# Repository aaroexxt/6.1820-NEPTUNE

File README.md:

# 6.1820-NEPTUNE
6.1820 final project - Aaron Becker and Nora Bulovic

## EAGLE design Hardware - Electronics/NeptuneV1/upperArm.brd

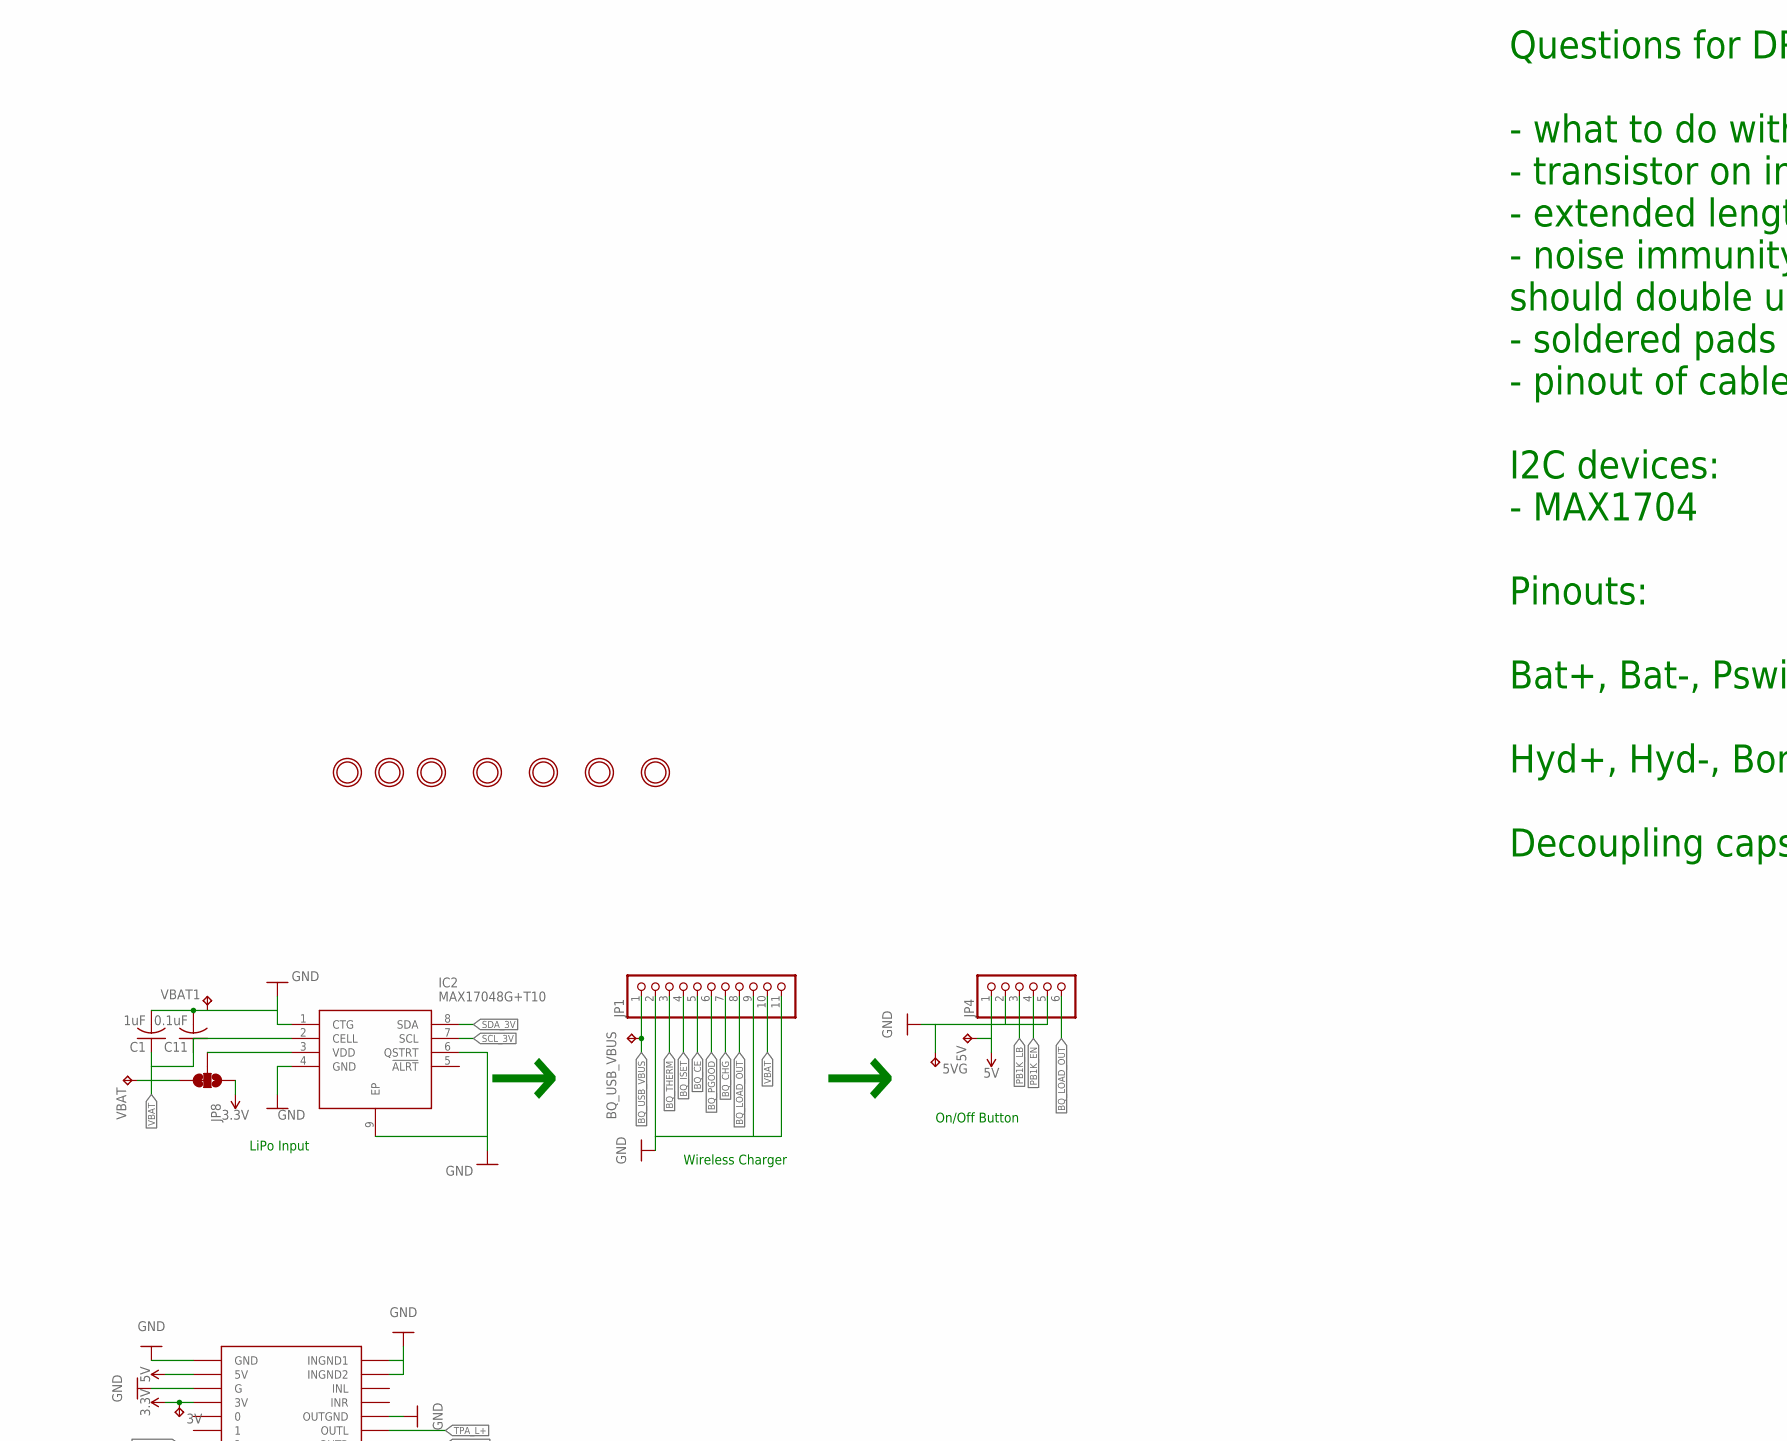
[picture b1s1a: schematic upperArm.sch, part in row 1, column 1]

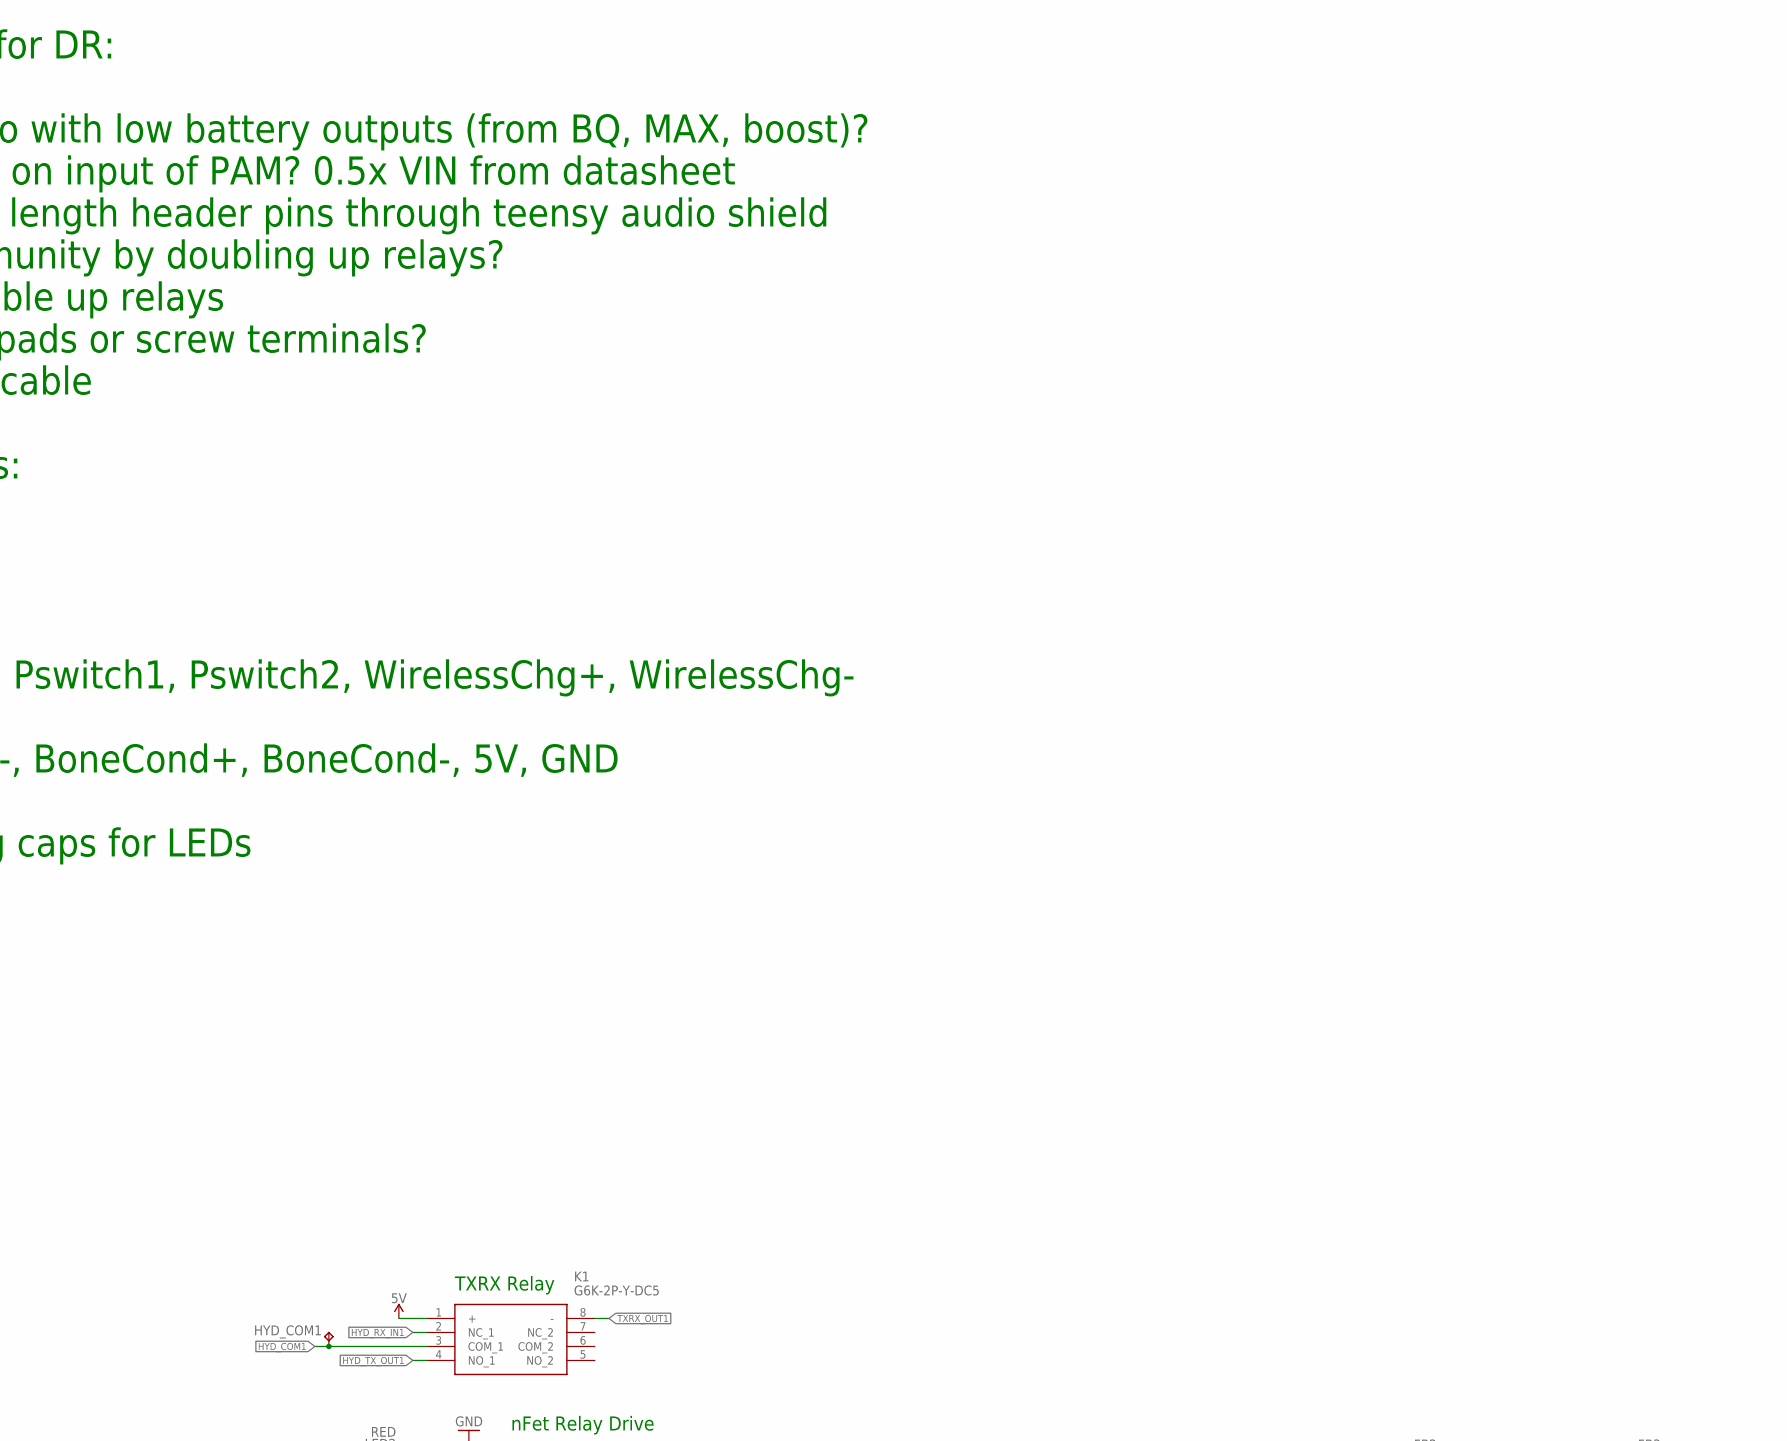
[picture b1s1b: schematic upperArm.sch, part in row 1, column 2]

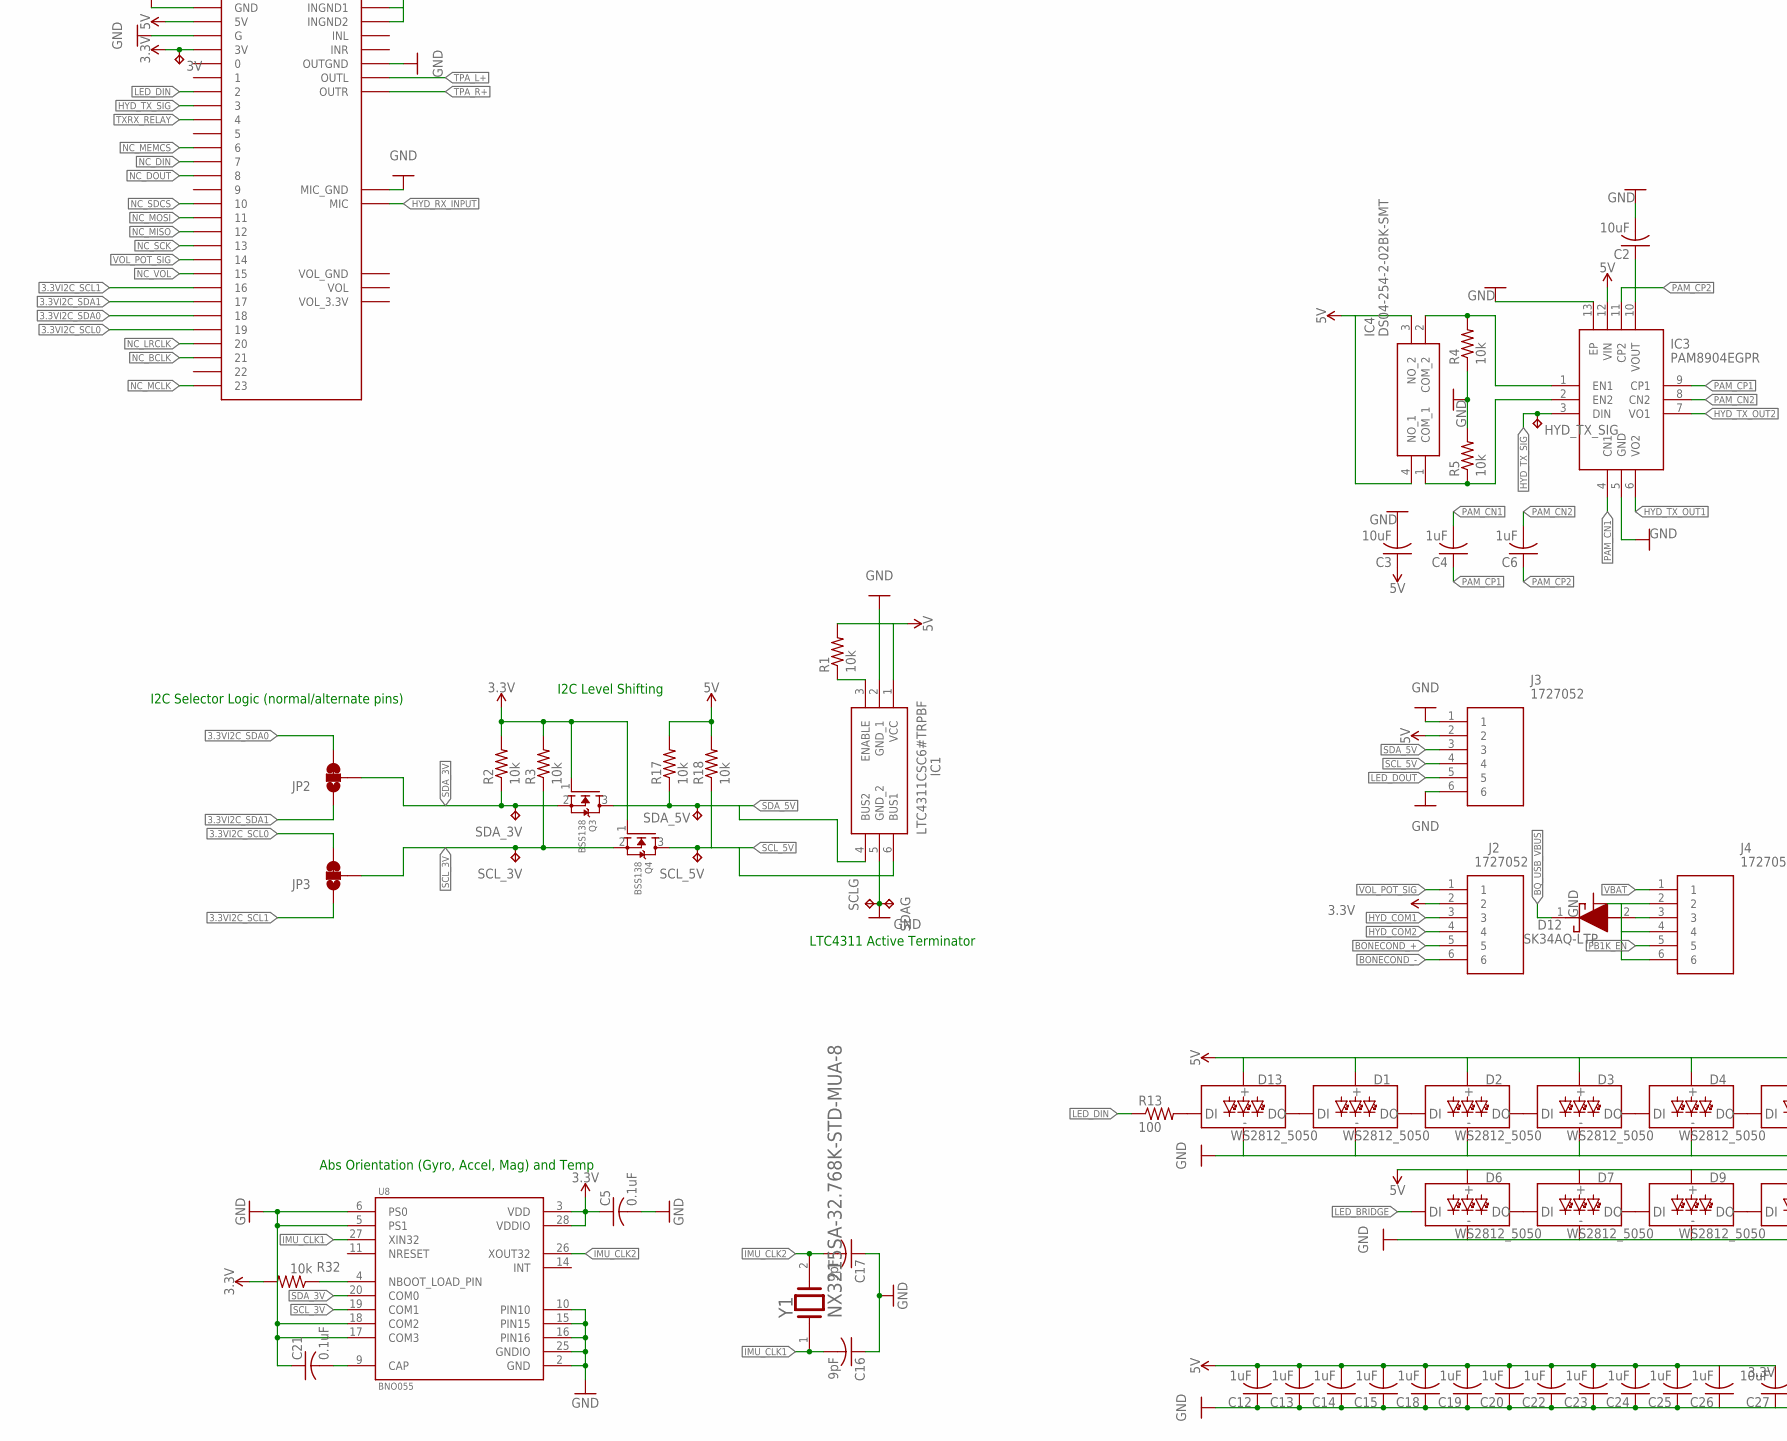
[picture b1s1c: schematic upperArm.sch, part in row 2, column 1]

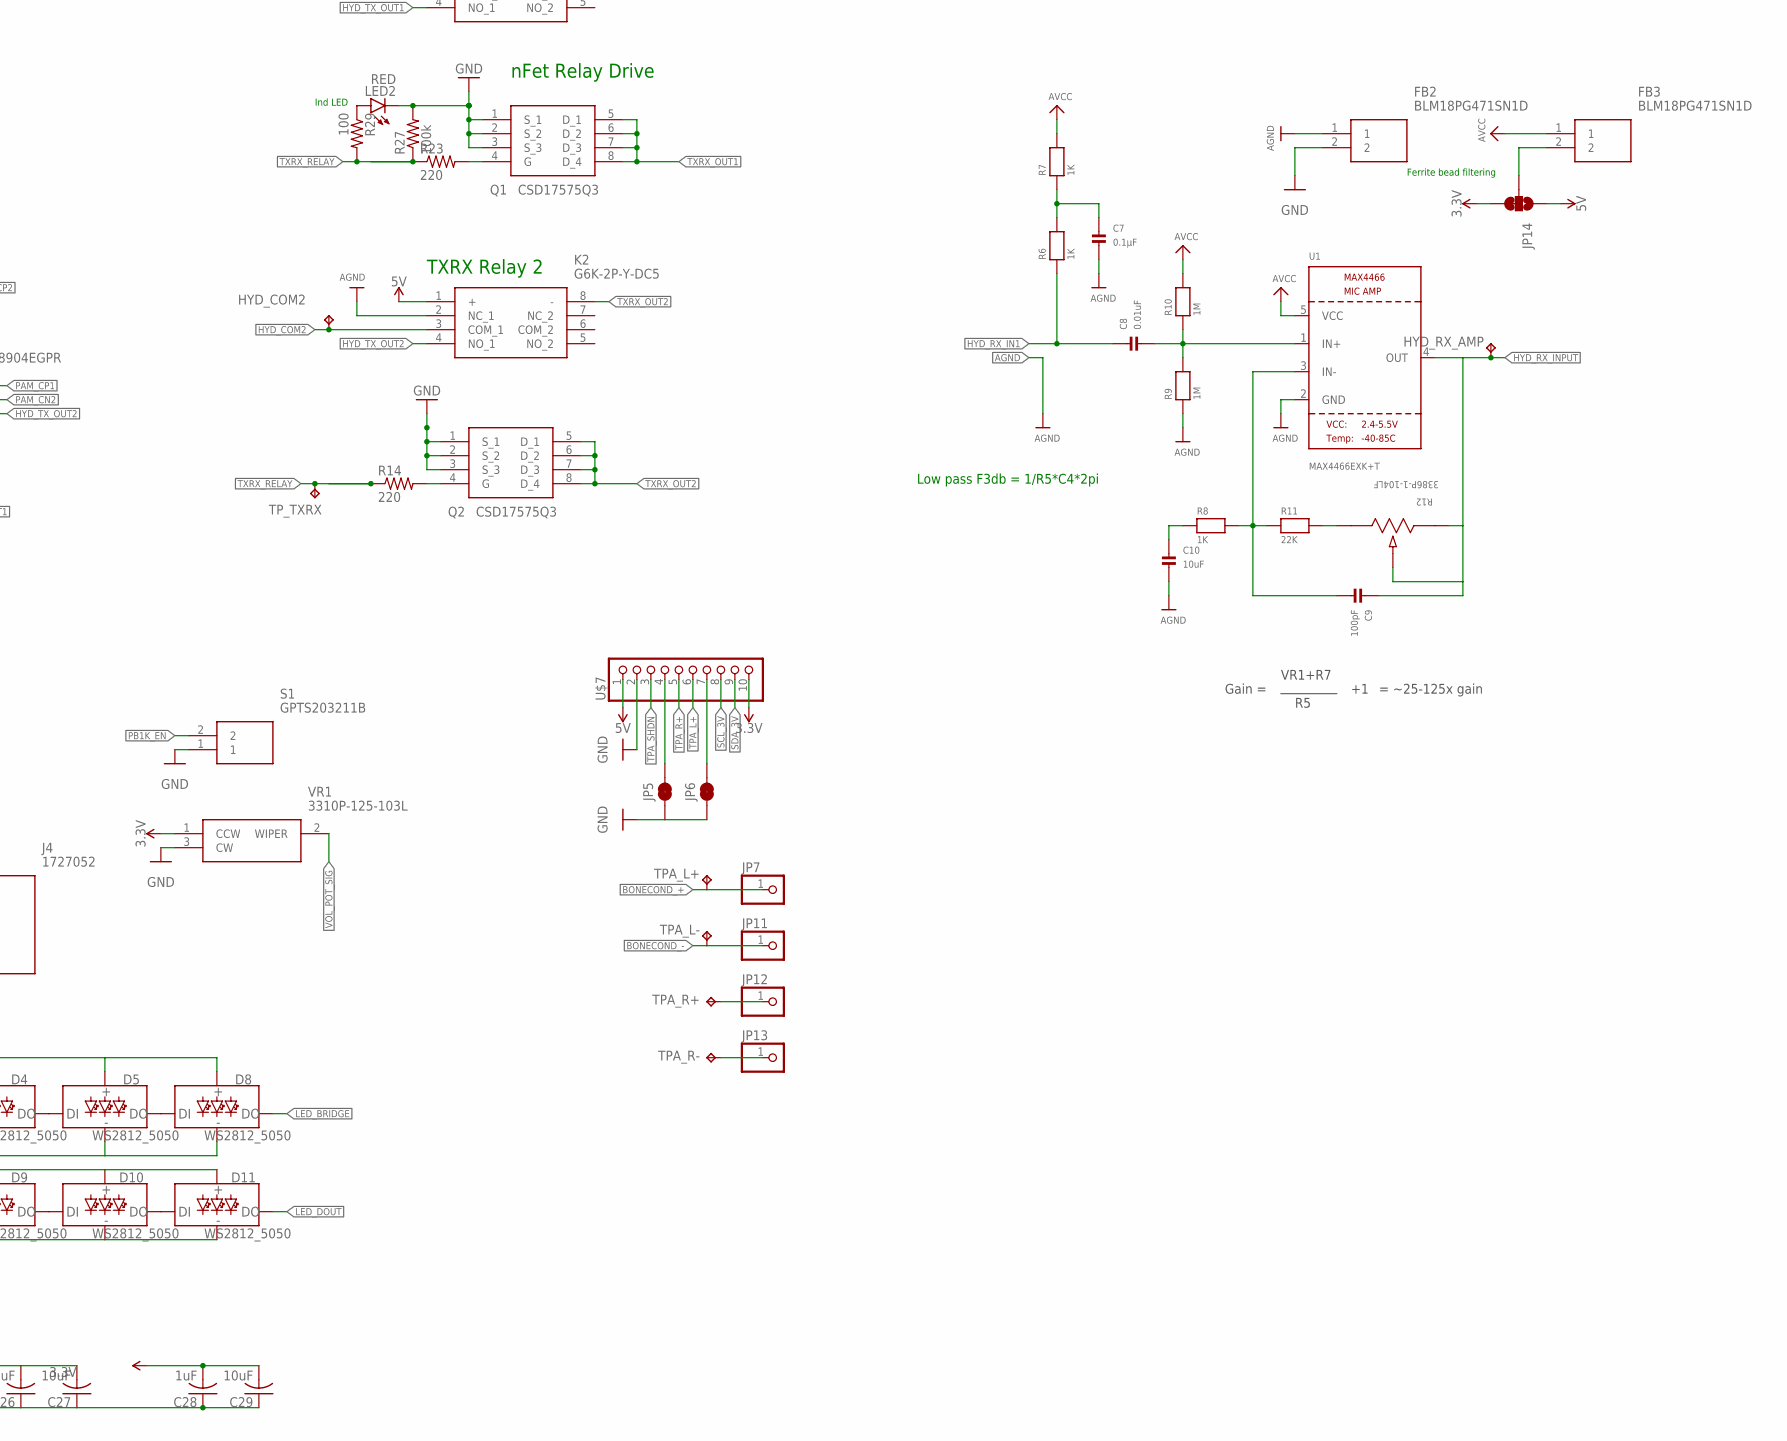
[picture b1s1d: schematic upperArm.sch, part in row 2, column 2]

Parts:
3V, 5V, 5VG: TPB1,27; B1,27
BQ_USB_VBUS: TPB1,27; B1,27
C1, C4, C6, C12, C13, C14, C15, C18, C19, C20, C22, C23, C24, C25, C26, C28: 1uF; C0805
C2, C3, C27, C29: 10uF; C0805
C5, C11, C21: 0.1uF; C0805
C7: 0.1µF; 0805
C8: 0.01uF; 0805
C9: 100pF; 0805
C10: 10uF; 0805
C16, C17: 9pF; C0805
D1, D2, D3, D4, D5, D6, D7, D8, D9, D10, D11, D13: WS2812_5050; WS2812-5X5-4PIN
D12: SK34AQ-LTP; DIOM5226X244N
FB2, FB3: BLM18PG471SN1D; BLM18SP221SN1B
HYD_COM1, HYD_COM2: TPB1,27; B1,27
HYD_RX_AMP: TPB1,27; B1,27
HYD_TX_SIG: TPB1,27; B1,27
IC1: LTC4311CSC6#TRPBF; SOT65P210X100-6N
IC2: MAX17048G+T10; SON50P200X200X80-9N
IC3: PAM8904EGPR; QFN40P200X200X80-13N
IC4: DS04-254-2-02BK-SMT; DS04254202BKSMT
J2, J3, J4: 1727052
JP1: PINHD-1X11; 1X11
JP2, JP3, JP8, JP14: JUMPER-SMT_3_1-NC_TRACE_NO-SILK; SMT-JUMPER_3_1-NC_TRACE_NO-SILK
JP4: PINHD-1X6; 1X06
JP5, JP6: JUMPER-SMT_2_NC_TRACE_NO-SILK; SMT-JUMPER_2_NC_TRACE_NO-SILK
JP7, JP11, JP12, JP13: PINHD-1X1; 1X01
K1, K2: G6K-2P-Y-DC5; G6K2PYDC12
LED2: RED; CHIP-LED0805
Q1, Q2: CSD17575Q3; CSD16327
Q3, Q4: BSS138; SOT23-WIDE
R1, R2, R3, R4, R5, R17, R18, R32: 10k; R0805
R6, R7, R8: 1K; 0805
R9, R10: 1M; 0805
R11: 22K; 0805
R12: 3386P-1-104LF; POT_3386P
R13: 100; R0603
R14, R23: 220; R0805
R27: 100k; R0805
R29: 100; R0805
S1: GPTS203211B
SCLG: TPB1,27; B1,27
SCL_3V, SCL_5V: TPB1,27; B1,27
SDAG: TPB1,27; B1,27
SDA_3V, SDA_5V: TPB1,27; B1,27
TPA_L+: TPB1,27; B1,27
TPA_L-: TPB1,27; B1,27
TPA_R+: TPB1,27; B1,27
TPA_R-: TPB1,27; B1,27
TP_TXRX: TPB1,27; B1,27
U1: MAX4466EXK+T; SC70-5
U8: BNO055; LGA28R50P4X10_380X520X100
U$1: AUDIOSHIELD
U$7: PINHD-1X10; 1X10
U$11, U$14, U$15, U$16, U$17, U$18, U$19: MOUNTINGHOLE2.5; MOUNTINGHOLE_2.5_PLATED
VBAT, VBAT1: TPB1,27; B1,27
VR1: 3310P-125-103L; 3310P125103L
Y1: NDK_NX3215SA-32.768K-STD-MUA-9; NDK_NX3215SA-32.768K-STD-MUA-8_0

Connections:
3.3V: 3V.TP, C5.1, C28.2, C29.2, J2.2, JP8.1, JP14.3, Q3.1 (G), Q4.1 (G), R2.2, R3.2, R32.2, U8.3 (VDD), U8.28 (VDDIO), U$1.3V, U$7.10, VR1.1 (CCW)
3.3VI2C_SCL0: JP3.3, U$1.19
3.3VI2C_SCL1: JP3.1, U$1.16
3.3VI2C_SDA0: JP2.3, U$1.18
3.3VI2C_SDA1: JP2.1, U$1.17
5V: 5V.TP, C3.1, C12.2, C13.2, C14.2, C15.2, C18.2, C19.2, C20.2, C22.2, C23.2, C24.2, C25.2, C26.2, C27.2, D1.VCC, D2.VCC, D3.VCC, D4.VCC, D5.VCC, D6.VCC, D7.VCC, D8.VCC, D9.VCC, D10.VCC, D11.VCC, D13.VCC, IC1.1 (VCC), IC3.12 (VIN), IC4.3 (NO_2), IC4.4 (NO_1), J3.2, JP4.1, JP14.1, K1.1 (+), K2.1 (+), R1.2, R17.2, R18.2, U$1.5V, U$7.1
AGND: C7.2, C10.2, FB2.1, K2.2 (NC_1), R9.1, U1.2 (GND)
AVCC: FB3.1, R7.2, R10.2, U1.5 (VCC)
BONECOND_+: J2.5, JP7.1, TPA_L+.TP
BONECOND_-: J2.6, JP11.1, TPA_L-.TP
BQ_CE: JP1.5
BQ_CHG: JP1.7
BQ_ISET: JP1.4
BQ_LOAD_OUT: JP1.8, JP4.6
BQ_PGOOD: JP1.6
BQ_THERM: JP1.3
BQ_USB_VBUS: BQ_USB_VBUS.TP, D12.1 (K), JP1.1
GND: 5VG.TP, C1.2, C2.2, C3.2, C5.2, C11.2, C12.1, C13.1, C14.1, C15.1, C16.1, C17.1, C18.1, C19.1, C20.1, C21.1, C22.1, C23.1, C24.1, C25.1, C26.1, C27.1, C28.1, C29.1, D1.GND, D2.GND, D3.GND, D4.GND, D5.GND, D6.GND, D7.GND, D8.GND, D9.GND, D10.GND, D11.GND, D13.GND, FB2.2, IC1.2 (GND_1), IC1.5 (GND_2), IC2.1 (CTG), IC2.4 (GND), IC2.6 (QSTRT), IC2.9 (EP), IC3.5 (GND), IC3.13 (EP), J3.1, J3.6, J4.2, J4.4, J4.6, JP1.2, JP1.9, JP1.11, JP4.2, JP4.5, JP5.1, JP6.1, LED2.C, Q1.1 (S_1), Q1.2 (S_2), Q1.3 (S_3), Q2.1 (S_1), Q2.2 (S_2), Q2.3 (S_3), R4.1, R5.2, R27.2, S1.1, SCLG.TP, SDAG.TP, U8.2 (GND), U8.5 (PS1), U8.6 (PS0), U8.10 (PIN10), U8.15 (PIN15), U8.16 (PIN16), U8.17 (COM3), U8.18 (COM2), U8.25 (GNDIO), U$1.G, U$1.GND, U$1.GND_MIC (MIC_GND), U$1.INGND1, U$1.INGND2, U$1.OUTGND, U$7.2, VBAT1.TP, VR1.3 (CW)
HYD_COM1: HYD_COM1.TP, J2.3, K1.3 (COM_1)
HYD_COM2: HYD_COM2.TP, J2.4, K2.3 (COM_1)
HYD_RX_IN1: C8.1, K1.2 (NC_1), R6.1
HYD_RX_INPUT: C9.1, HYD_RX_AMP.TP, R12.1, R12.2, U1.4 (OUT), U$1.MIC
HYD_TX_OUT1: IC3.6 (VO2), K1.4 (NO_1)
HYD_TX_OUT2: IC3.7 (VO1), K2.4 (NO_1)
HYD_TX_SIG: HYD_TX_SIG.TP, IC3.3 (DIN), U$1.3
IMU_CLK1: C16.2, U8.27 (XIN32), Y1.1
IMU_CLK2: C17.2, U8.26 (XOUT32), Y1.2
LED_BRIDGE: D6.DI, D8.DO
LED_DIN: R13.1, U$1.2
LED_DOUT: D11.DO, J3.5
unnamed: IC1.3 (ENABLE), R1.1
unnamed: JP12.1, TPA_R+.TP
unnamed: JP13.1, TPA_R-.TP
unnamed: D6.DO, D7.DI
unnamed: IC2.3 (VDD), JP8.2
unnamed: Q2.4 (G), R14.2
unnamed: C2.1, IC3.10 (VOUT)
unnamed: D13.DI, R13.2
unnamed: JP5.2, U$7.4
unnamed: D1.DO, D2.DI
unnamed: IC3.1 (EN1), IC4.2 (COM_2), R4.2
unnamed: IC3.2 (EN2), IC4.1 (COM_1), R5.1
unnamed: FB3.2, JP14.2
unnamed: C7.1, R6.2, R7.1
unnamed: C8.2, R9.2, R10.1, U1.1 (IN+)
unnamed: D1.DI, D13.DO
unnamed: C9.2, R8.2, R11.1, U1.3 (IN-)
unnamed: C10.1, R8.1
unnamed: R11.2, R12.3
unnamed: D12.2 (A), J4.3
unnamed: D2.DO, D3.DI
unnamed: D3.DO, D4.DI
unnamed: D4.DO, D5.DI
unnamed: D5.DO, D8.DI
unnamed: D7.DO, D9.DI
unnamed: D9.DO, D10.DI
unnamed: D10.DO, D11.DI
unnamed: JP6.2, U$7.7
unnamed: C21.2, U8.9 (CAP)
unnamed: R32.1, U8.4 (NBOOT_LOAD_PIN)
unnamed: Q1.4 (G), R23.2
unnamed: LED2.A, R29.1
NC_BCLK: U$1.21
NC_DIN: U$1.7
NC_DOUT: U$1.8
NC_LRCLK: U$1.20
NC_MCLK: U$1.23
NC_MEMCS: U$1.6
NC_MISO: U$1.12
NC_MOSI: U$1.11
NC_SCK: U$1.13
NC_SDCS: U$1.10
NC_VOL: U$1.15
PAM_CN1: C4.2, IC3.4 (CN1)
PAM_CN2: C6.2, IC3.8 (CN2)
PAM_CP1: C4.1, IC3.9 (CP1)
PAM_CP2: C6.1, IC3.11 (CP2)
PB1K_EN: J4.5, JP4.4, S1.2
PB1K_LB: JP4.3
SCL_3V: IC2.7 (SCL), JP3.2, Q4.2 (S), R3.1, SCL_3V.TP, U8.19 (COM1), U$7.8
SCL_5V: IC1.6 (BUS1), J3.4, Q4.3 (D), R18.1, SCL_5V.TP
SDA_3V: IC2.8 (SDA), JP2.2, Q3.2 (S), R2.1, SDA_3V.TP, U8.20 (COM0), U$7.9
SDA_5V: IC1.4 (BUS2), J3.3, Q3.3 (D), R17.1, SDA_5V.TP
TPA_L+: U$1.OUTL, U$7.6
TPA_R+: U$1.OUTR, U$7.5
TPA_SHDN: U$7.3
TXRX_OUT1: K1.8 (-), Q1.5 (D_1), Q1.6 (D_2), Q1.7 (D_3), Q1.8 (D_4)
TXRX_OUT2: K2.8 (-), Q2.5 (D_1), Q2.6 (D_2), Q2.7 (D_3), Q2.8 (D_4)
TXRX_RELAY: R14.1, R23.1, R27.1, R29.2, TP_TXRX.TP, U$1.4
VBAT: C1.1, C11.1, IC2.2 (CELL), J4.1, JP1.10, JP8.3, VBAT.TP
VOL_POT_SIG: J2.1, U$1.14, VR1.2 (WIPER)

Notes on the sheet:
I2C Level Shifting
Abs Orientation (Gyro, Accel, Mag) and Temp
I2C Selector Logic (normal/alternate pins)
LTC4311 Active Terminator
Wireless Charger
On/Off Button
Questions for DR: - what to do with low battery outputs (from BQ, MAX, boost)? - transistor on input of PAM? 0.5x VIN from datasheet - extended length header pins through teensy audio shield - noise immunity by doubling up relays? should double up relays - soldered pads or screw terminals? - pinout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
LiPo Input
Gain =
VR1+R7
= ~25-125x gain
Low pass F3db = 1/R5*C4*2pi
nFet Relay Drive
Ind LED
TXRX Relay
Ferrite bead filtering
TXRX Relay 2

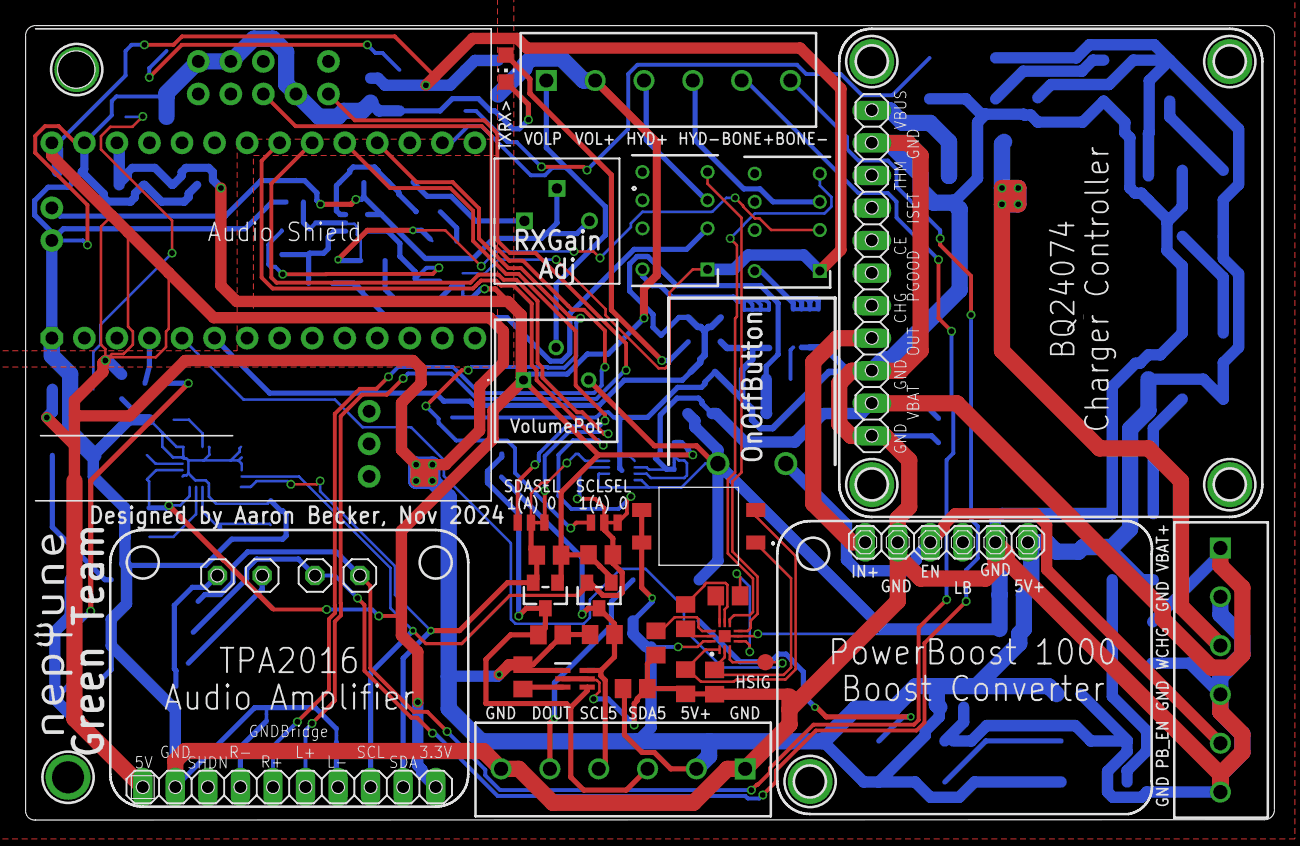
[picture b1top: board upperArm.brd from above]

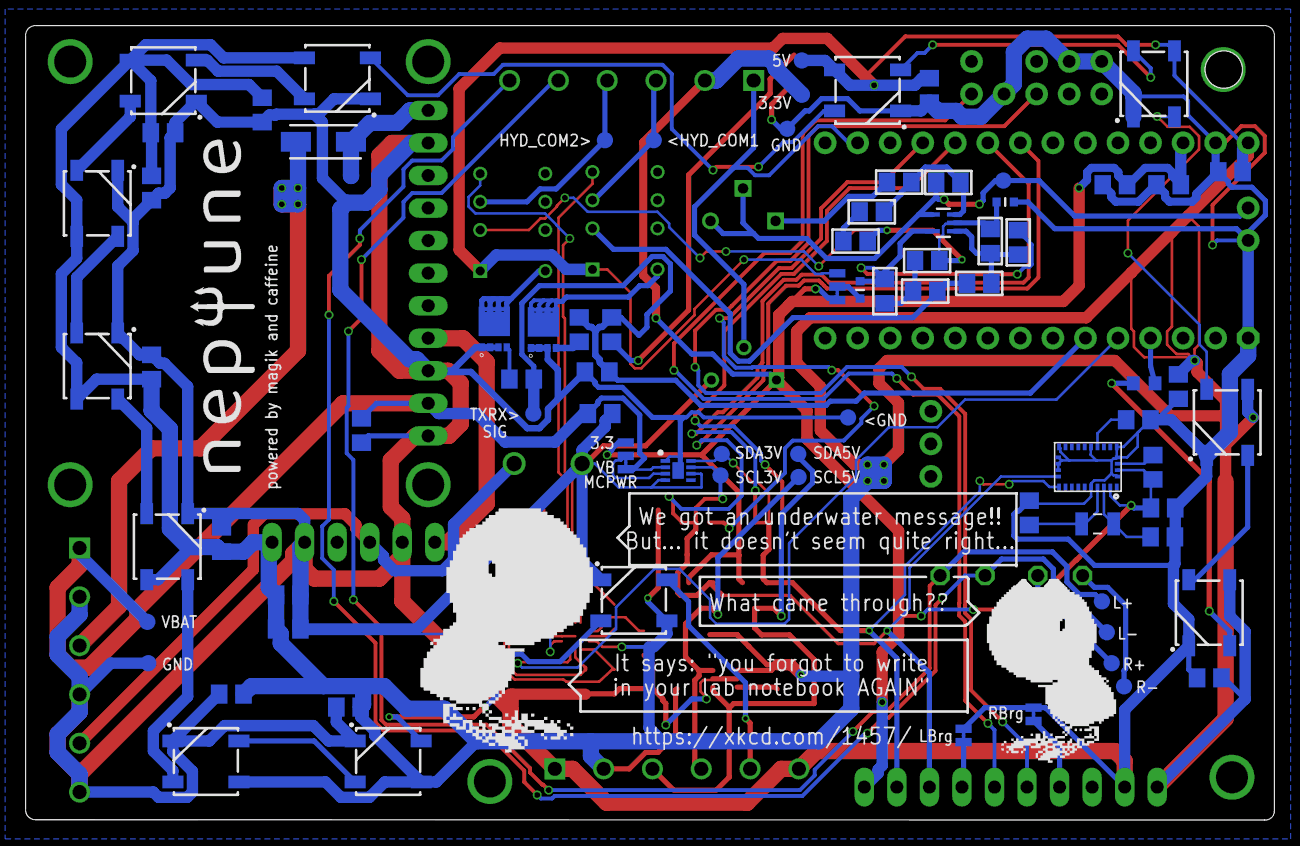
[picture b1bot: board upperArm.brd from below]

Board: 2 copper layers, 97.5 x 62.0 mm, 125 parts (82 on the bottom side), 73 nets.

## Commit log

2025-04-03 all PCBs and old software!
2025-04-03 diagrams and commented code for transitioning
2025-04-03 skeleton code for Neptune-Reader
2025-04-10 paper started, code semi updated, solid modelling
2025-04-11 CAD and protocol description
2025-04-11 hamming message
2025-04-12 slight protocol update
2025-04-12 SECDED update (single error correction, double error detection)
2025-04-12 compiling neptune node!
2025-04-12 all da test scripts (ironically untested)
2025-04-12 aaaand bugfixes done! all scripts ready
2025-04-12 latenight semi tex update
2025-04-12 changes from full day of testing!
2025-04-13 major code cleanup and rewrite AGAIN
2025-04-13 quick command change and debug mode add
2025-04-18 box v2 updates!
2025-05-01 CAD updates final (cover, counterbores)
2025-05-01 Merging changes from Nora
2025-05-06 Test UI updates from Nora
2025-05-07 fixes from more testing
2025-05-07 errorRateAnalysis
2025-05-07 Final updates to UI (pseudorandom bit strings)
2025-05-08 BP filtering to bit counter mode
2025-05-10 Final edits and changes from testing

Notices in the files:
parts and their libraries:
microbuilder: This work is placed in the public domain, and may be freely used for commercial and non-commercial work with the following conditions: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
SparkFun-Jumpers: Licensing: Creative Commons ShareAlike 4.0 International - https://creativecommons.org/licenses/by-sa/4.0
